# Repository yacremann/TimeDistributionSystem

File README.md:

# Time Distribution System for Lab Based Experiments

This project implements a time distribution system for laboratory based experiments using pulsed lasers.
It consists of a transmitter and several receivers. The transmitter generates a unique pulse-id number for
each laser pulse. This pulse-id, together with configuration information is transmitted to the receivers
over twisted-pair cables (use Cat 6A cables only!). A magnetic RAM is used to store the last value and to
recover after a power outage.

The receivers decode the pulse-id send it to FPGAs on individual instruments (framegrabber boards, digitizers, ...)
for time stamping the data. In addition, the receivers generate low-jitter trigger signals. These can be configured
from the transmitter.

The project contains the following components:
- Boards: Schematics and layouts of the printed circuit boards for the receiver and transmitter
- Firmware: Logic on the FPGAs as well as firmware running on an embedded RISC-V processor for the transmitter and receivers
- Tango: Device servers for the transmitter and to configure the trigger channels of the receivers (see tango-controls.org)
- Notes: Presentation with the block diagrams of the system

## Requirements:
- For simulating the individual components of the firmware: Cocotb, Verilator
- For synthesis: Quartus (intel) v. 23.1 standard edition
- For the software on the RISC-V: gcc for RV32IM (see https://github.com/SpinalHDL/VexRiscv)
- Tango control system: https://tango-controls.org

The project contains the following 3rd party components:
Firmware:
- CRC generator (https://github.com/hellgate202/crc_calc.git)
- Softcore: Based on the VexRiscV project (https://github.com/SpinalHDL/VexRiscv)
- TinyDuino_lib: developed by Domenic Wüthrich as a semester project at ETH Zurich, institute for integrated systems.
- fifo_v3: https://github.com/pulp-platform/common_cells/blob/master/src/fifo_v3.sv (ETH Zurich and University of Bologna)

License:
GNU Public License v3.0 (see LICENSE)

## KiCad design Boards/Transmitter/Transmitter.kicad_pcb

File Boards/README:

This is the schematic and layout of the time distribution system. It consists of a transmitter and a receiver board. A detailed description will be published in a paper.

This part has been developed by Jingo Bozzini and Yves Acremann at the Physics Department of ETH Zurich, Switzerland.
acremann@solid.phys.ethz.ch

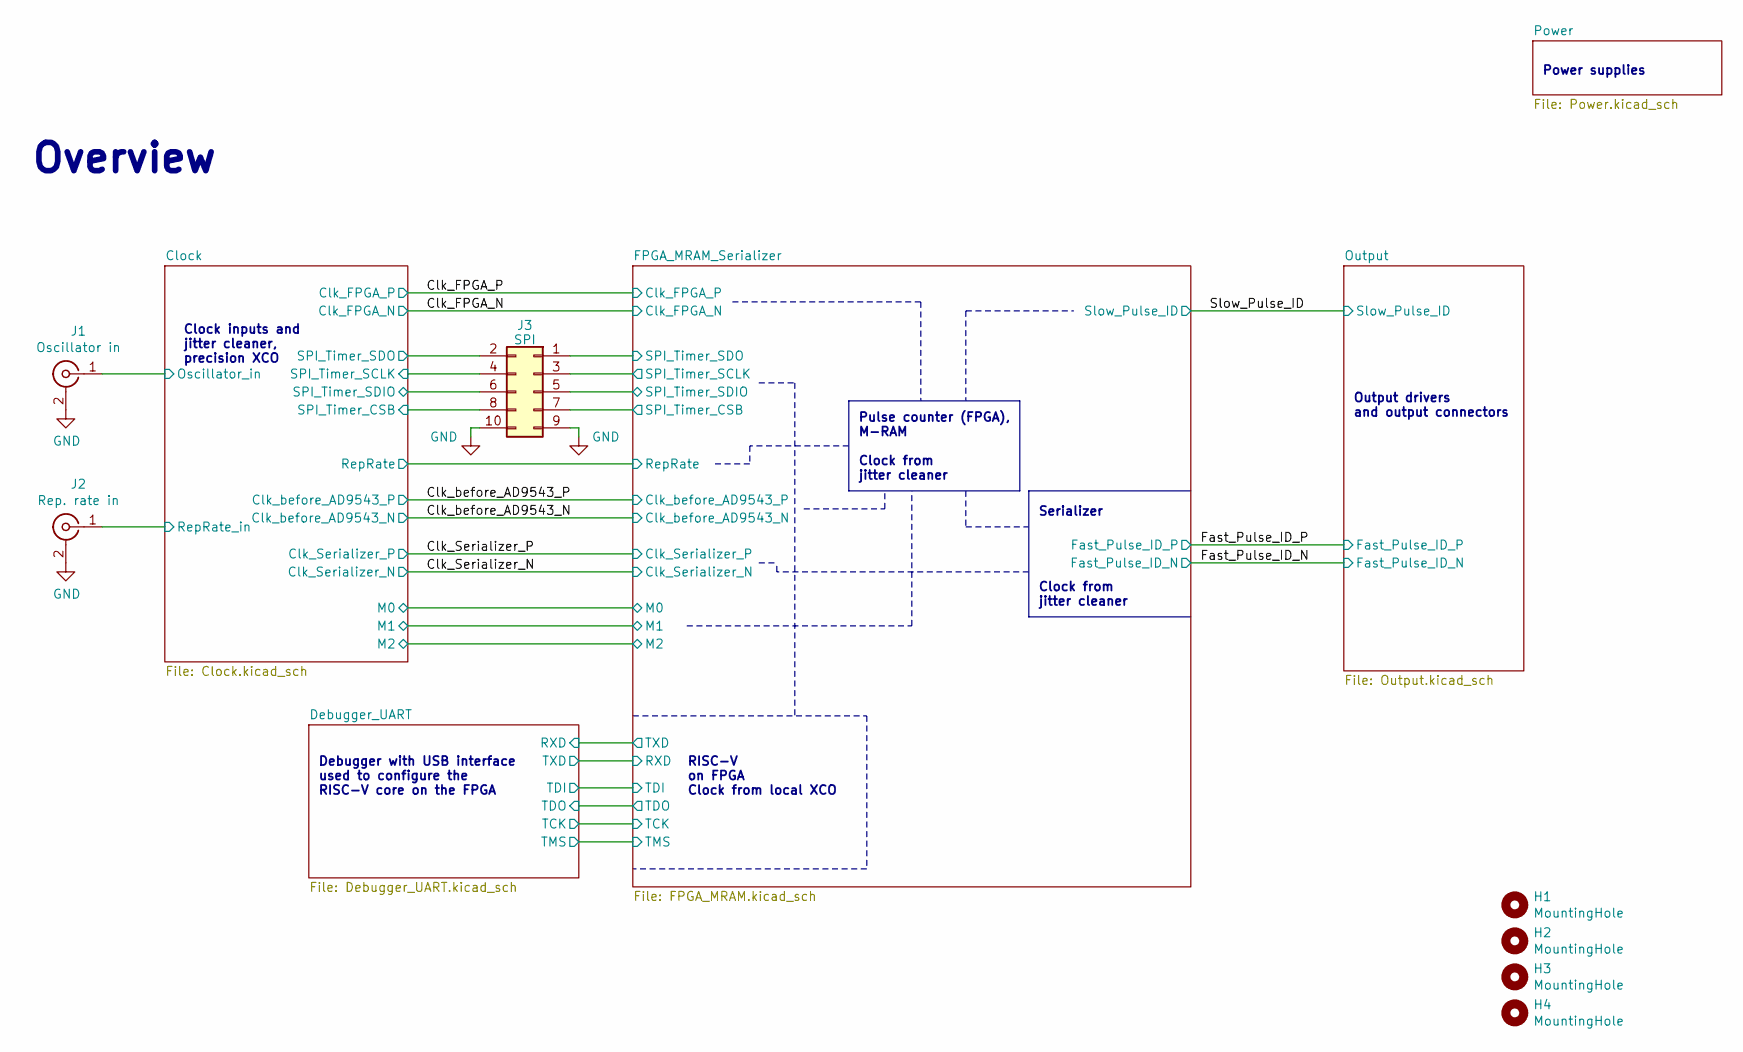
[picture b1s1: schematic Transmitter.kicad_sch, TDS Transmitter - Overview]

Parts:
H1, H2, H3, H4: MountingHole; MountingHole_2.7mm_M2.5
J1: Oscillator in; SMA_Amphenol_132289_EdgeMount
J2: Rep. rate in; SMA_Amphenol_132289_EdgeMount
J3: SPI; PinHeader_2x05_P2.54mm_Vertical

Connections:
/Clock/Oscillator_in: J1.1 (In); also elsewhere on the board
/Clock/RepRate_in: J2.1 (In); also elsewhere on the board
/Clock/SPI_Timer_CSB: J3.8; also elsewhere on the board
/Clock/SPI_Timer_SCLK: J3.4; also elsewhere on the board
/Clock/SPI_Timer_SDIO: J3.6; also elsewhere on the board
/Clock/SPI_Timer_SDO: J3.2; also elsewhere on the board
/FPGA_MRAM_Serializer/SPI_Timer_CSB: J3.7; also elsewhere on the board
/FPGA_MRAM_Serializer/SPI_Timer_SCLK: J3.3; also elsewhere on the board
/FPGA_MRAM_Serializer/SPI_Timer_SDIO: J3.5; also elsewhere on the board
/FPGA_MRAM_Serializer/SPI_Timer_SDO: J3.1; also elsewhere on the board
GND: J1.2 (Ext), J2.2 (Ext), J3.9, J3.10; also elsewhere on the board

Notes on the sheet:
RISC-V on FPGA Clock from local XCO
Pulse counter (FPGA), M-RAM Clock from jitter cleaner
Clock inputs and jitter cleaner, precision XCO
Clock from jitter cleaner
Overview
Power supplies
Debugger with USB interface used to configure the RISC-V core on the FPGA
Output drivers and output connectors
Serializer

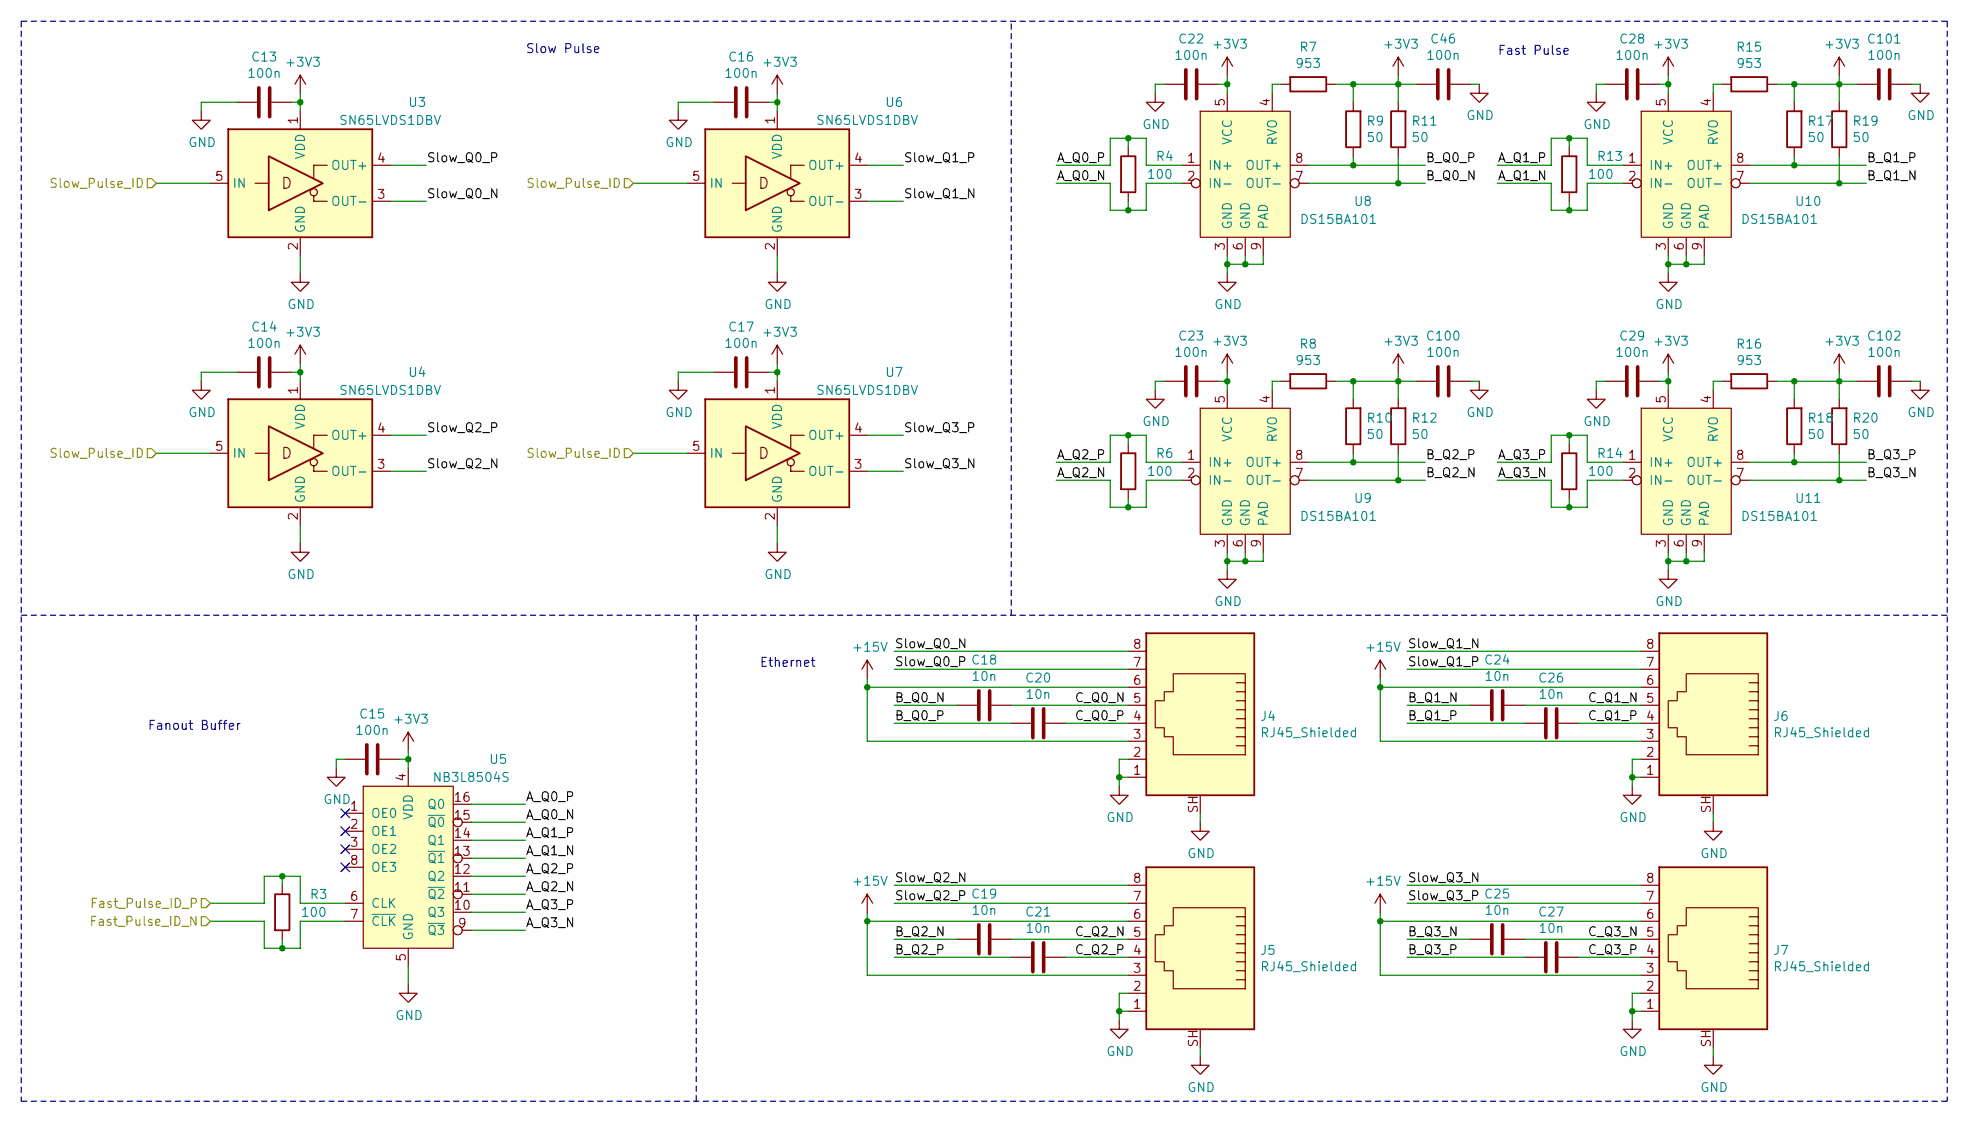
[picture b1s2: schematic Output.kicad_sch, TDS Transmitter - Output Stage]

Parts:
C13, C14, C15, C16, C17, C22, C23, C28, C29, C46, C100, C101, C102: 100n; C_0603_1608Metric
C18, C19, C20, C21, C24, C25, C26, C27: 10n; C_0603_1608Metric
J4, J5, J6, J7: RJ45_Shielded; RJ45_Amphenol_RJHSE5380
R3, R4, R6, R13, R14: 100; R_0402_1005Metric
R7, R8, R15, R16: 953; R_0603_1608Metric
R9, R10, R11, R12, R17, R18, R19, R20: 50; R_0603_1608Metric
U3, U4, U6, U7: SN65LVDS1DBV; SOT-23-5
U5: NB3L8504S; TSSOP-16_4.4x5mm_P0.65mm
U8, U9, U10, U11: DS15BA101; WSON-8-1EP_3x3mm_P0.5mm_EP1.6x2.0mm

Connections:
+3V3: C13.1, C14.1, C15.1, C16.1, C17.1, C22.1, C23.1, C28.1, C29.1, C46.2, C100.2, C101.2, C102.2, R7.1, R8.1, R9.2, R10.2, R11.2, R12.2, R15.1, R16.1, R17.2, R18.2, R19.2, R20.2, U3.1 (VDD), U4.1 (VDD), U5.4 (VDD), U6.1 (VDD), U7.1 (VDD), U8.5 (VCC), U9.5 (VCC), U10.5 (VCC), U11.5 (VCC); also elsewhere on the board
+15V: J4.3, J4.6, J5.3, J5.6, J6.3, J6.6, J7.3, J7.6; also elsewhere on the board
/Fast_Pulse_ID_N: R3.2, U5.7 (~CLK); also elsewhere on the board
/Fast_Pulse_ID_P: R3.1, U5.6 (CLK); also elsewhere on the board
/Output/A_Q0_N: R4.2, U5.15 (~Q0), U8.2 (IN-)
/Output/A_Q0_P: R4.1, U5.16 (Q0), U8.1 (IN+)
/Output/A_Q1_N: R13.2, U5.13 (~Q1), U10.2 (IN-)
/Output/A_Q1_P: R13.1, U5.14 (Q1), U10.1 (IN+)
/Output/A_Q2_N: R6.2, U5.11 (~Q2), U9.2 (IN-)
/Output/A_Q2_P: R6.1, U5.12 (Q2), U9.1 (IN+)
/Output/A_Q3_N: R14.2, U5.9 (~Q3), U11.2 (IN-)
/Output/A_Q3_P: R14.1, U5.10 (Q3), U11.1 (IN+)
/Output/B_Q0_N: C18.2, R11.1, U8.7 (OUT-)
/Output/B_Q0_P: C20.2, R9.1, U8.8 (OUT+)
/Output/B_Q1_N: C24.2, R19.1, U10.7 (OUT-)
/Output/B_Q1_P: C26.2, R17.1, U10.8 (OUT+)
/Output/B_Q2_N: C19.2, R12.1, U9.7 (OUT-)
/Output/B_Q2_P: C21.2, R10.1, U9.8 (OUT+)
/Output/B_Q3_N: C25.2, R20.1, U11.7 (OUT-)
/Output/B_Q3_P: C27.2, R18.1, U11.8 (OUT+)
/Output/C_Q0_N: C18.1, J4.5
/Output/C_Q0_P: C20.1, J4.4
/Output/C_Q1_N: C24.1, J6.5
/Output/C_Q1_P: C26.1, J6.4
/Output/C_Q2_N: C19.1, J5.5
/Output/C_Q2_P: C21.1, J5.4
/Output/C_Q3_N: C25.1, J7.5
/Output/C_Q3_P: C27.1, J7.4
/Output/Slow_Q0_N: J4.8, U3.3 (OUT-)
/Output/Slow_Q0_P: J4.7, U3.4 (OUT+)
/Output/Slow_Q1_N: J6.8, U6.3 (OUT-)
/Output/Slow_Q1_P: J6.7, U6.4 (OUT+)
/Output/Slow_Q2_N: J5.8, U4.3 (OUT-)
/Output/Slow_Q2_P: J5.7, U4.4 (OUT+)
/Output/Slow_Q3_N: J7.8, U7.3 (OUT-)
/Output/Slow_Q3_P: J7.7, U7.4 (OUT+)
/Slow_Pulse_ID: U3.5 (IN), U4.5 (IN), U6.5 (IN), U7.5 (IN); also elsewhere on the board
GND: C13.2, C14.2, C15.2, C16.2, C17.2, C22.2, C23.2, C28.2, C29.2, C46.1, C100.1, C101.1, C102.1, J4.1, J4.2, J4.SH, J5.1, J5.2, J5.SH, J6.1, J6.2, J6.SH, J7.1, J7.2, J7.SH, U3.2 (GND), U4.2 (GND), U5.5 (GND), U6.2 (GND), U7.2 (GND), U8.3 (GND), U8.6 (GND), U8.9 (PAD), U9.3 (GND), U9.6 (GND), U9.9 (PAD), U10.3 (GND), U10.6 (GND), U10.9 (PAD), U11.3 (GND), U11.6 (GND), U11.9 (PAD); also elsewhere on the board
unnamed: R7.2, U8.4 (RVO)
unnamed: R8.2, U9.4 (RVO)
unnamed: R15.2, U10.4 (RVO)
unnamed: R16.2, U11.4 (RVO)

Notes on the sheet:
Slow Pulse
Fanout Buffer
Fast Pulse
Ethernet

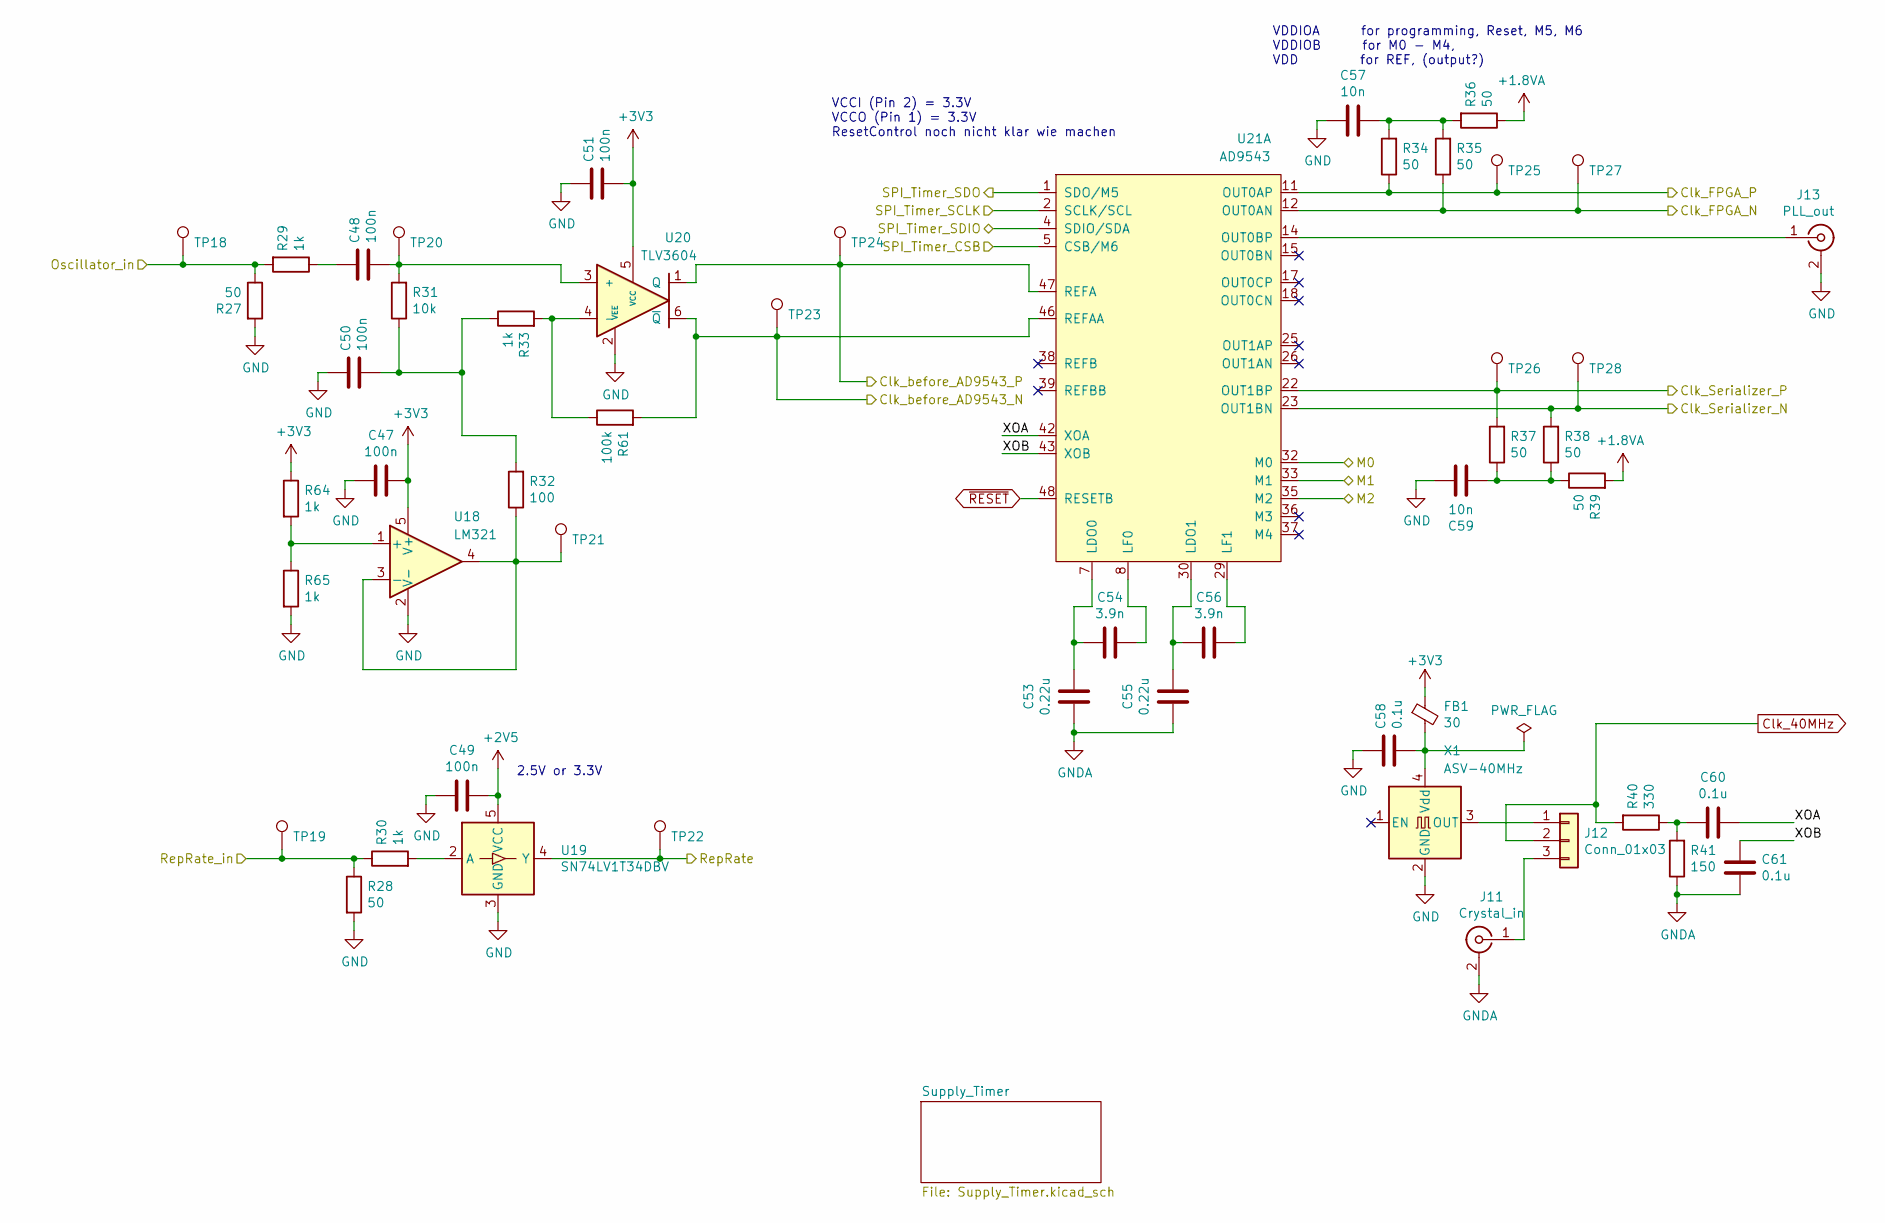
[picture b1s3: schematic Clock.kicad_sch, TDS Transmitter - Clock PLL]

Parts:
C47, C48, C49, C50, C51: 100n; C_0603_1608Metric
C53, C55: 0.22u; C_0603_1608Metric
C54, C56: 3.9n; C_0603_1608Metric
C57, C59: 10n; C_0603_1608Metric
C58: 0.1u; C_0603_1608Metric
C60, C61: 0.1u; C_0402_1005Metric
FB1: 30; L_0402_1005Metric
J11: Crystal_in; SMA_Amphenol_901-144_Vertical
J12: Conn_01x03; PinHeader_1x03_P2.54mm_Vertical
J13: PLL_out; SMA_Amphenol_901-144_Vertical
R27, R28, R34, R35, R36, R37, R38, R39: 50; R_0603_1608Metric
R29, R30, R33, R64, R65: 1k; R_0603_1608Metric
R31: 10k; R_0603_1608Metric
R32: 100; R_0603_1608Metric
R40: 330; R_0603_1608Metric
R41: 150; R_0603_1608Metric
R61: 100k; R_0603_1608Metric
TP18, TP19, TP20, TP21, TP22, TP23, TP24, TP25, TP26, TP27, TP28: TestPoint; TestPoint_THTPad_D1.5mm_Drill0.7mm
U18: LM321; SOT-353_SC-70-5_Handsoldering
U19: SN74LV1T34DBV; SOT-23-5
U20: TLV3604; R-PDSO-G6
U21: AD9543; LFCSP-48-1EP_7x7mm_P0.5mm_EP4.1x4.1mm
X1: ASV-40MHz; Oscillator_SMD_Abracon_ASV-4Pin_7.0x5.1mm

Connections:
+1V0: R36.1, R39.2; also elsewhere on the board
+2V5: C49.1, U19.5 (VCC); also elsewhere on the board
+3V3: C47.1, C51.2, FB1.1, R64.1, U18.5 (V+), U20.5 (VCC); also elsewhere on the board
/Clk_FPGA_N: R35.1, TP27.1, U21.12 (OUT0AN); also elsewhere on the board
/Clk_FPGA_P: R34.1, TP25.1, U21.11 (OUT0AP); also elsewhere on the board
/Clk_Serializer_N: R38.2, TP28.1, U21.23 (OUT1BN); also elsewhere on the board
/Clk_Serializer_P: R37.2, TP26.1, U21.22 (OUT1BP); also elsewhere on the board
/Clk_before_AD9543_N: R61.2, TP23.1, U20.6 (~Q), U21.46 (REFAA); also elsewhere on the board
/Clk_before_AD9543_P: TP24.1, U20.1 (Q), U21.47 (REFA); also elsewhere on the board
/Clock/M0: U21.32 (M0); also elsewhere on the board
/Clock/M1: U21.33 (M1); also elsewhere on the board
/Clock/M2: U21.35 (M2); also elsewhere on the board
/Clock/Oscillator_in: R27.1, R29.2, TP18.1; also elsewhere on the board
/Clock/RepRate: TP22.1, U19.4 (Y); also elsewhere on the board
/Clock/RepRate_in: R28.1, R30.1, TP19.1; also elsewhere on the board
/Clock/SPI_Timer_CSB: U21.5 (CSB/M6); also elsewhere on the board
/Clock/SPI_Timer_SCLK: U21.2 (SCLK/SCL); also elsewhere on the board
/Clock/SPI_Timer_SDIO: U21.4 (SDIO/SDA); also elsewhere on the board
/Clock/SPI_Timer_SDO: U21.1 (SDO/M5); also elsewhere on the board
/Clock/XOA: C60.1, U21.42 (XOA)
/Clock/XOB: C61.2, U21.43 (XOB)
Clk_40MHz: J12.2, R40.2; also elsewhere on the board
GND: C47.2, C49.2, C50.1, C51.1, C57.2, C58.2, C59.1, J13.2 (Ext), R27.2, R28.2, R65.2, U18.2 (V-), U19.3 (GND), U20.2 (VEE), X1.2 (GND); also elsewhere on the board
GNDA: C53.2, C55.2, C61.1, J11.2 (Ext), R41.1; also elsewhere on the board
unnamed: C48.1, R29.1
unnamed: C48.2, R31.2, TP20.1, U20.3 (+)
unnamed: C50.2, R31.1, R32.2, R33.1
unnamed: C53.1, C54.2, U21.7 (LDO0)
unnamed: C54.1, U21.8 (LF0)
unnamed: C55.1, C56.2, U21.30 (LDO1)
unnamed: C56.1, U21.29 (LF1)
unnamed: C57.1, R34.2, R35.2, R36.2
unnamed: C58.1, FB1.2, X1.4 (Vdd)
unnamed: C59.2, R37.1, R38.1, R39.1
unnamed: C60.2, R40.1, R41.2
unnamed: J11.1 (In), J12.3
unnamed: J12.1, X1.3 (OUT)
unnamed: J13.1 (In), U21.14 (OUT0BP)
unnamed: R30.2, U19.2 (A)
unnamed: R32.1, TP21.1, U18.3 (-), U18.4
unnamed: R33.2, R61.1, U20.4 (-)
unnamed: R64.2, R65.1, U18.1 (+)
~RESET: U21.48 (RESETB); also elsewhere on the board

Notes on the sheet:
2.5V or 3.3V
VDDIOA for programming, Reset, M5, M6 VDDIOB for M0 - M4, VDD for REF, (output?)
VCCI (Pin 2) = 3.3V VCCO (Pin 1) = 3.3V ResetControl noch nicht klar wie machen

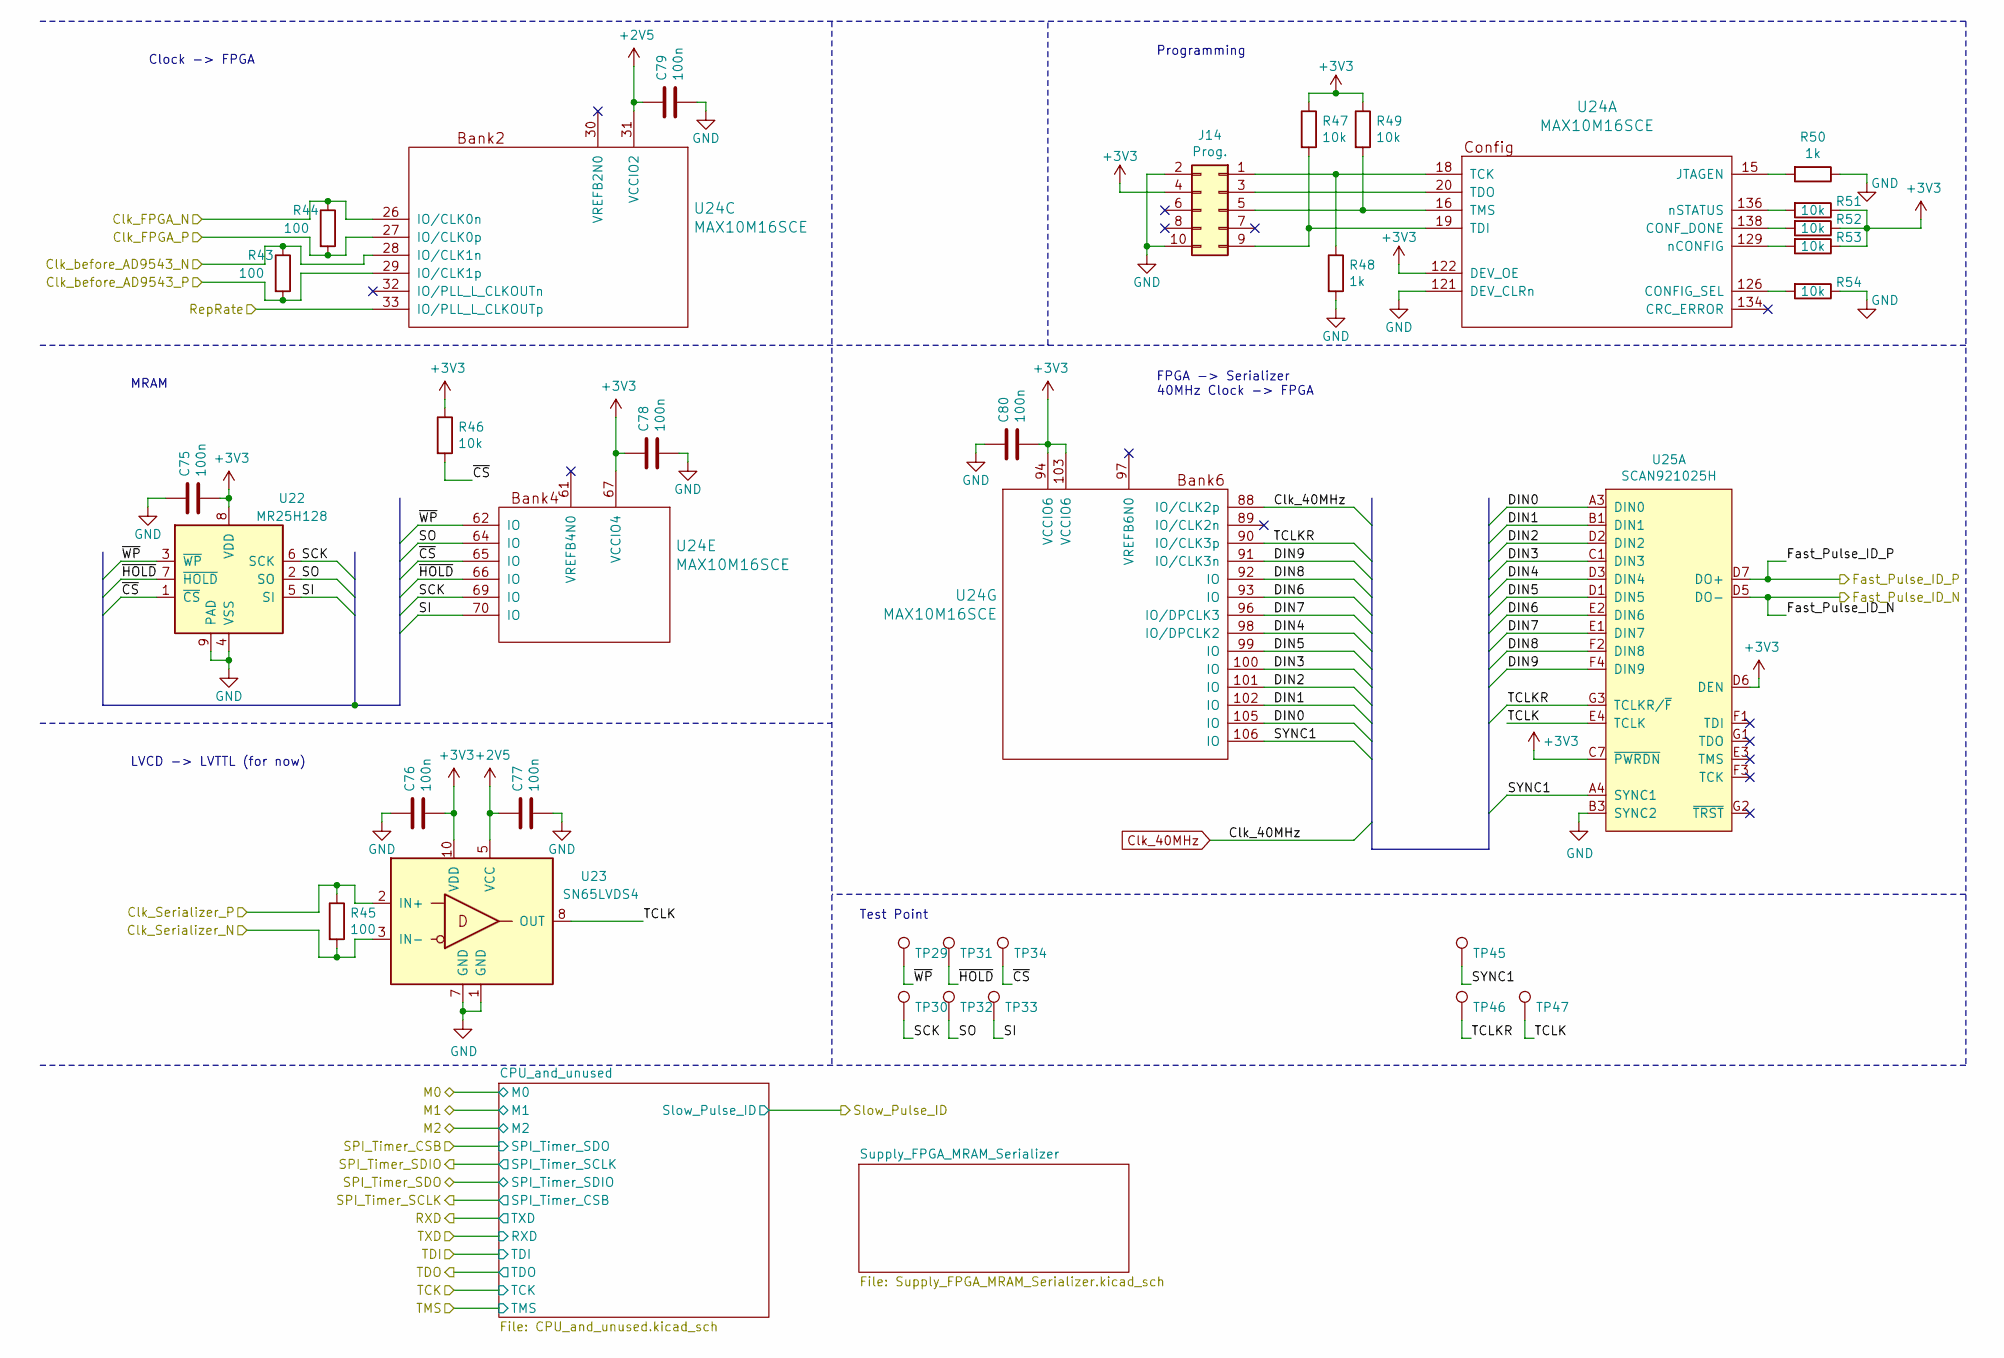
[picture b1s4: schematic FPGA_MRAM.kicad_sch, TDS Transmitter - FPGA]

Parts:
C75, C76, C77, C78, C79, C80: 100n; C_0603_1608Metric
J14: Prog.; IDC-Header_2x05_P2.54mm_Vertical
R43, R44, R45: 100; R_0402_1005Metric
R46, R47, R49, R51, R52, R53, R54: 10k; R_0603_1608Metric
R48, R50: 1k; R_0603_1608Metric
TP29, TP30, TP31, TP32, TP33, TP34, TP45, TP46, TP47: TestPoint; TestPoint_THTPad_D1.5mm_Drill0.7mm
U22: MR25H128; DFN-8-1EP_6x5mm_P1.27mm_EP2x2mm
U23: SN65LVDS4; Texas_R-PUQFN-N10
U24: MAX10M16SCE; EQFP_144
U25: SCAN921025H; BGA-49_7x7_7.0x7.0mm

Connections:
+2V5: C77.1, C79.1, U23.5 (VCC), U24.31 (VCCIO2); also elsewhere on the board
+3V3: C75.2, C76.2, C78.1, C80.2, J14.4, R46.1, R47.1, R49.1, R51.1, R52.1, R53.1, U22.8 (VDD), U23.10 (VDD), U24.67 (VCCIO4), U24.94 (VCCIO6), U24.103 (VCCIO6), U24.122 (DEV_OE), U25.C7 (~PWRDN), U25.D6 (DEN); also elsewhere on the board
/Clk_FPGA_N: R44.1, U24.26 (IO/CLK0n); also elsewhere on the board
/Clk_FPGA_P: R44.2, U24.27 (IO/CLK0p); also elsewhere on the board
/Clk_Serializer_N: R45.2, U23.3 (IN-); also elsewhere on the board
/Clk_Serializer_P: R45.1, U23.2 (IN+); also elsewhere on the board
/Clk_before_AD9543_N: R43.1, U24.28 (IO/CLK1n); also elsewhere on the board
/Clk_before_AD9543_P: R43.2, U24.29 (IO/CLK1p); also elsewhere on the board
/Clock/RepRate: U24.33 (IO/PLL_L_CLKOUTp); also elsewhere on the board
/FPGA_MRAM_Serializer/DIN0: U24.105 (IO), U25.A3 (DIN0)
/FPGA_MRAM_Serializer/DIN1: U24.102 (IO), U25.B1 (DIN1)
/FPGA_MRAM_Serializer/DIN2: U24.101 (IO), U25.D2 (DIN2)
/FPGA_MRAM_Serializer/DIN3: U24.100 (IO), U25.C1 (DIN3)
/FPGA_MRAM_Serializer/DIN4: U24.98 (IO/DPCLK2), U25.D3 (DIN4)
/FPGA_MRAM_Serializer/DIN5: U24.99 (IO), U25.D1 (DIN5)
/FPGA_MRAM_Serializer/DIN6: U24.93 (IO), U25.E2 (DIN6)
/FPGA_MRAM_Serializer/DIN7: U24.96 (IO/DPCLK3), U25.E1 (DIN7)
/FPGA_MRAM_Serializer/DIN8: U24.92 (IO), U25.F2 (DIN8)
/FPGA_MRAM_Serializer/DIN9: U24.91 (IO/CLK3n), U25.F4 (DIN9)
/FPGA_MRAM_Serializer/SCK: TP30.1, U22.6 (SCK), U24.69 (IO)
/FPGA_MRAM_Serializer/SI: TP33.1, U22.5 (SI), U24.70 (IO)
/FPGA_MRAM_Serializer/SO: TP32.1, U22.2 (SO), U24.64 (IO)
/FPGA_MRAM_Serializer/SYNC1: TP45.1, U24.106 (IO), U25.A4 (SYNC1)
/FPGA_MRAM_Serializer/TCLK: TP47.1, U23.8 (OUT), U25.E4 (TCLK)
/FPGA_MRAM_Serializer/TCLKR: TP46.1, U24.90 (IO/CLK3p), U25.G3 (TCLKR/~F)
/FPGA_MRAM_Serializer/~CS: R46.2, TP34.1, U22.1 (~CS), U24.65 (IO)
/FPGA_MRAM_Serializer/~HOLD: TP31.1, U22.7 (~HOLD), U24.66 (IO)
/FPGA_MRAM_Serializer/~WP: TP29.1, U22.3 (~WP), U24.62 (IO)
/Fast_Pulse_ID_N: U25.D5 (DO-); also elsewhere on the board
/Fast_Pulse_ID_P: U25.D7 (DO+); also elsewhere on the board
Clk_40MHz: U24.88 (IO/CLK2p); also elsewhere on the board
GND: C75.1, C76.1, C77.2, C78.2, C79.2, C80.1, J14.2, J14.10, R48.2, R50.1, R54.1, U22.4 (VSS), U22.9 (PAD), U23.1 (GND), U23.7 (GND), U24.121 (DEV_CLRn), U25.B3 (SYNC2); also elsewhere on the board
unnamed: J14.1, R48.1, U24.18 (TCK)
unnamed: J14.3, U24.20 (TDO)
unnamed: J14.5, R49.2, U24.16 (TMS)
unnamed: J14.9, R47.2, U24.19 (TDI)
unnamed: R50.2, U24.15 (JTAGEN)
unnamed: R51.2, U24.136 (nSTATUS)
unnamed: R52.2, U24.138 (CONF_DONE)
unnamed: R53.2, U24.129 (nCONFIG)
unnamed: R54.2, U24.126 (CONFIG_SEL)

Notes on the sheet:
Programming
FPGA -> Serializer 40MHz Clock -> FPGA
Test Point
LVCD -> LVTTL (for now)
MRAM
Clock -> FPGA

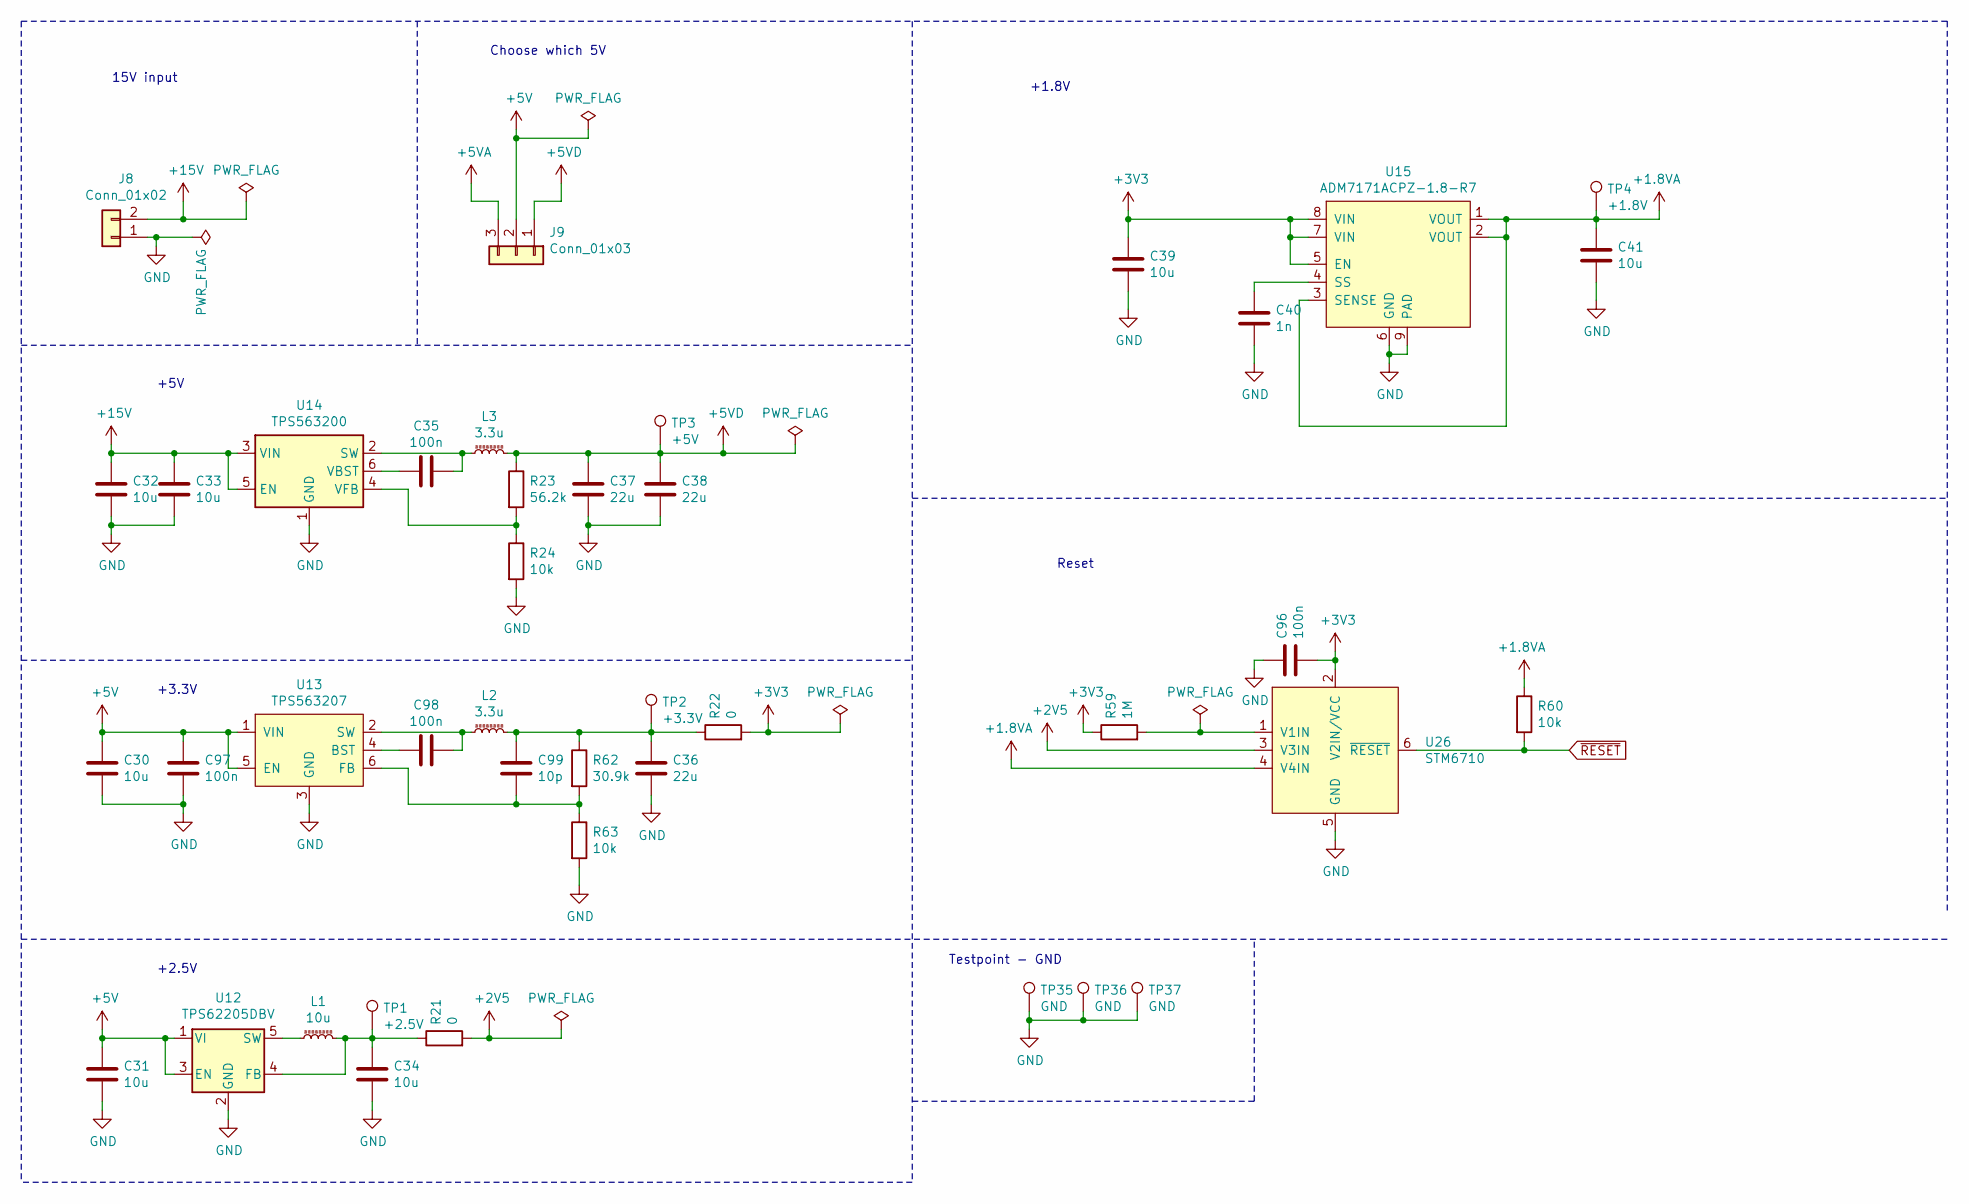
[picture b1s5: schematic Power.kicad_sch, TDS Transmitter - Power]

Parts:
C30, C31, C32, C33, C34, C39, C41: 10u; C_0603_1608Metric
C35, C96, C97, C98: 100n; C_0603_1608Metric
C36, C37, C38: 22u; C_0603_1608Metric
C40: 1n; C_0603_1608Metric
C99: 10p; C_0603_1608Metric
J8: Conn_01x02; 3.81mm_2_pos
J9: Conn_01x03; PinHeader_1x03_P2.54mm_Vertical
L1: 10u; L_1008_2520Metric
L2, L3: 3.3u; L_Bourns-SRN8040_8x8.15mm
R21: 0; R_0603_1608Metric
R22: 0; R_1206_3216Metric
R23: 56.2k; R_0603_1608Metric
R24, R60, R63: 10k; R_0603_1608Metric
R59: 1M; R_0603_1608Metric
R62: 30.9k; R_0603_1608Metric
TP1: +2.5V; TestPoint_THTPad_D1.5mm_Drill0.7mm
TP2: +3.3V; TestPoint_THTPad_D1.5mm_Drill0.7mm
TP3: +5V; TestPoint_THTPad_D1.5mm_Drill0.7mm
TP4: +1.8V; TestPoint_THTPad_D1.5mm_Drill0.7mm
TP35, TP36, TP37: GND; TestPoint_THTPad_D1.5mm_Drill0.7mm
U12: TPS62205DBV; SOT-23-5
U13: TPS563207; SOT-563
U14: TPS563200; SOT-23-6
U15: ADM7171ACPZ-1.8-R7; LFCSP-8-1EP_3x3mm_P0.5mm_EP1.45x1.74mm
U26: STM6710; SOT-23-6

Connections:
+1V0: C41.1, R60.1, TP4.1, U15.1 (VOUT), U15.2 (VOUT), U15.3 (SENSE), U26.4 (V4IN); also elsewhere on the board
+2V5: R21.2, U26.3 (V3IN); also elsewhere on the board
+3V3: C39.1, C96.2, R22.2, R59.1, U15.5 (EN), U15.7 (VIN), U15.8 (VIN), U26.2 (V2IN/VCC); also elsewhere on the board
+5V: C30.1, C31.1, C97.1, J9.2, U12.1 (VI), U12.3 (EN), U13.1 (VIN), U13.5 (EN)
+5VA: J9.3; also elsewhere on the board
+5VD: C37.1, C38.1, J9.1, L3.2, R23.1, TP3.1
+15V: C32.1, C33.1, J8.2, U14.3 (VIN), U14.5 (EN); also elsewhere on the board
GND: C30.2, C31.2, C32.2, C33.2, C34.2, C36.2, C37.2, C38.2, C39.2, C40.2, C41.2, C96.1, C97.2, J8.1, R24.2, R63.2, TP35.1, TP36.1, TP37.1, U12.2 (GND), U13.3 (GND), U14.1 (GND), U15.6 (GND), U15.9 (PAD), U26.5 (GND); also elsewhere on the board
unnamed: C34.1, L1.2, R21.1, TP1.1, U12.4 (FB)
unnamed: C35.1, L3.1, U14.2 (SW)
unnamed: C35.2, U14.6 (VBST)
unnamed: C36.1, C99.1, L2.2, R22.1, R62.1, TP2.1
unnamed: C40.1, U15.4 (SS)
unnamed: C98.1, L2.1, U13.2 (SW)
unnamed: C98.2, U13.4 (BST)
unnamed: C99.2, R62.2, R63.1, U13.6 (FB)
unnamed: L1.1, U12.5 (SW)
unnamed: R23.2, R24.1, U14.4 (VFB)
unnamed: R59.2, U26.1 (V1IN)
~RESET: R60.2, U26.6 (~RESET); also elsewhere on the board

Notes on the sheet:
+2.5V
Testpoint - GND
+5V
+1.8V
Reset
Choose which 5V
15V input
+3.3V

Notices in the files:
Boards/Receiver/CDR_PLL.kicad_sch:
(c) 2025 ETH Zurich, Y. Acremann
Boards/Receiver/Receiver.kicad_pcb:
(c) 2025 ETH Zurich, J. Bozzini, Y. Acremann
